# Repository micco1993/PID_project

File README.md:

# PID_project
Android and Arduino projects for making a simple PID controller.

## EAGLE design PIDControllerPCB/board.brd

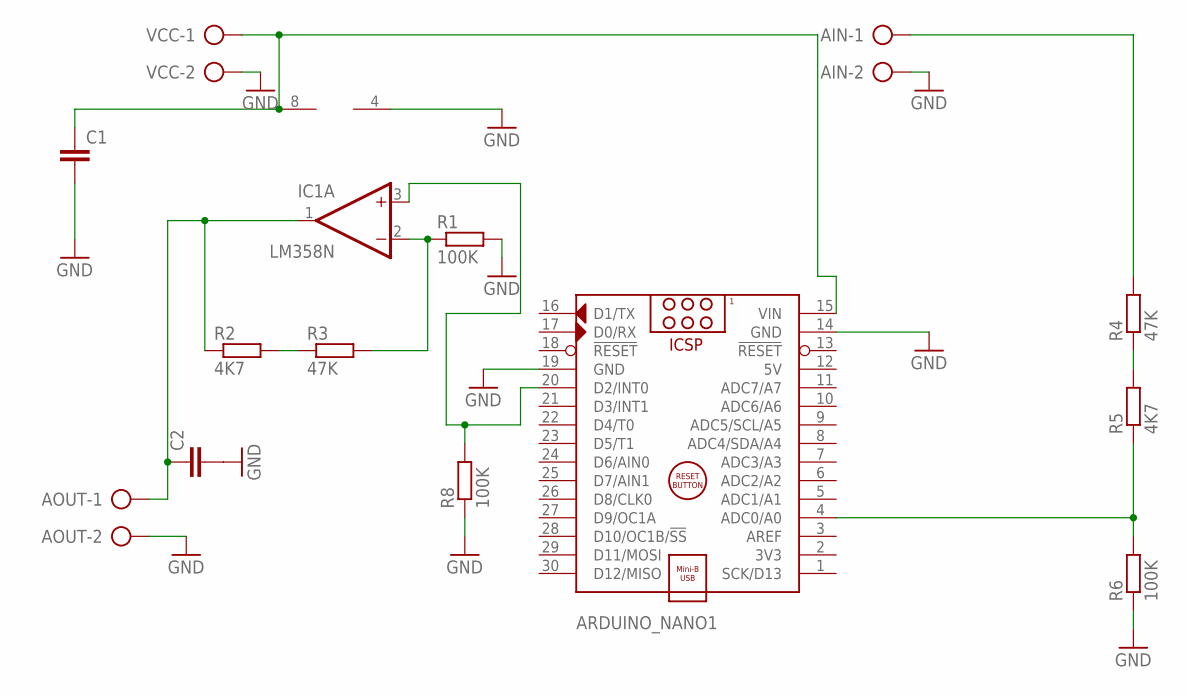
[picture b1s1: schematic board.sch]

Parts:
AIN: AK300/2
AOUT: AK300/2
ARDUINO_NANO1: ARDUINO_NANO
C1, C2: C5/5; C5B5
IC1: LM358N; DIL08
R1, R6, R8: 100K; 0207/10
R2, R5: 4K7; 0207/10
R3, R4: 47K; 0207/10
VCC: AK300/2

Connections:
5V: ARDUINO_NANO1.12 (5V)
GND: AIN.2, AOUT.2, ARDUINO_NANO1.14 (GND), ARDUINO_NANO1.19 (GND), C1.2, C2.2, IC1.4 (V-), R1.2, R6.1, R8.1, VCC.2
unnamed: ARDUINO_NANO1.15 (VIN), C1.1, IC1.8 (V+), VCC.1
unnamed: AIN.1, R4.2
unnamed: IC1.2 (-IN), R1.1, R3.2
unnamed: AOUT.1, C2.1, IC1.1 (OUT), R2.1
unnamed: R2.2, R3.1
unnamed: ARDUINO_NANO1.20 (D2/INT0), IC1.3 (+IN), R8.2
unnamed: R4.1, R5.2
unnamed: ARDUINO_NANO1.4 (ADC0/A0), R5.1, R6.2

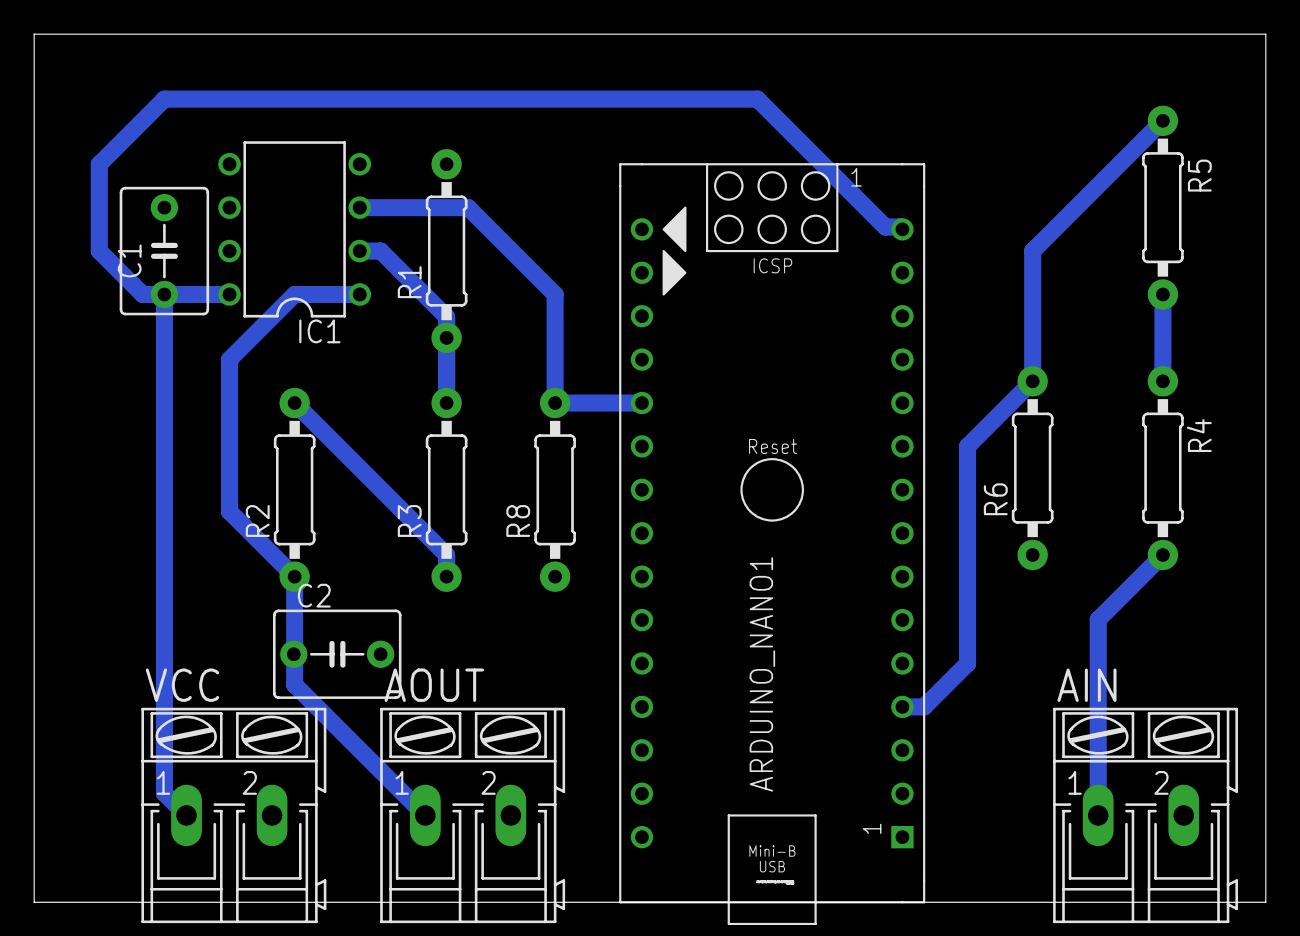
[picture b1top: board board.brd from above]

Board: 2 copper layers, 72.1 x 50.8 mm, 14 parts (0 on the bottom side), 9 nets.

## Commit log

2023-03-27 Add PID Controller Android project
2023-04-14 Arduino project added
2023-04-14 Add EAGLE project files and Gerber files for the PCB
2023-04-23 Added About App section to application
2023-04-23 Added license.txt
2023-04-24 Change units for csv file and add instructions for Android app
